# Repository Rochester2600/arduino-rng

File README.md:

Arduino random number generator using sha1 for hammering in randomness wether we need it or
want it.

The calibration routing is from the orignal code and helps deal with things that happen
to transistors as they aged. Find a micro-E for an actual explanation that makes sense.

NOTE:
If you change the transistor to something with a different reverse bias threshold, the entire
thing can either get better or fall apart completely

Original project README
=============================================================================================

Arduino True Random Number Generator
----

Instructions for constructing the circuit can be found here: http://robseward.com/misc/RNG2/

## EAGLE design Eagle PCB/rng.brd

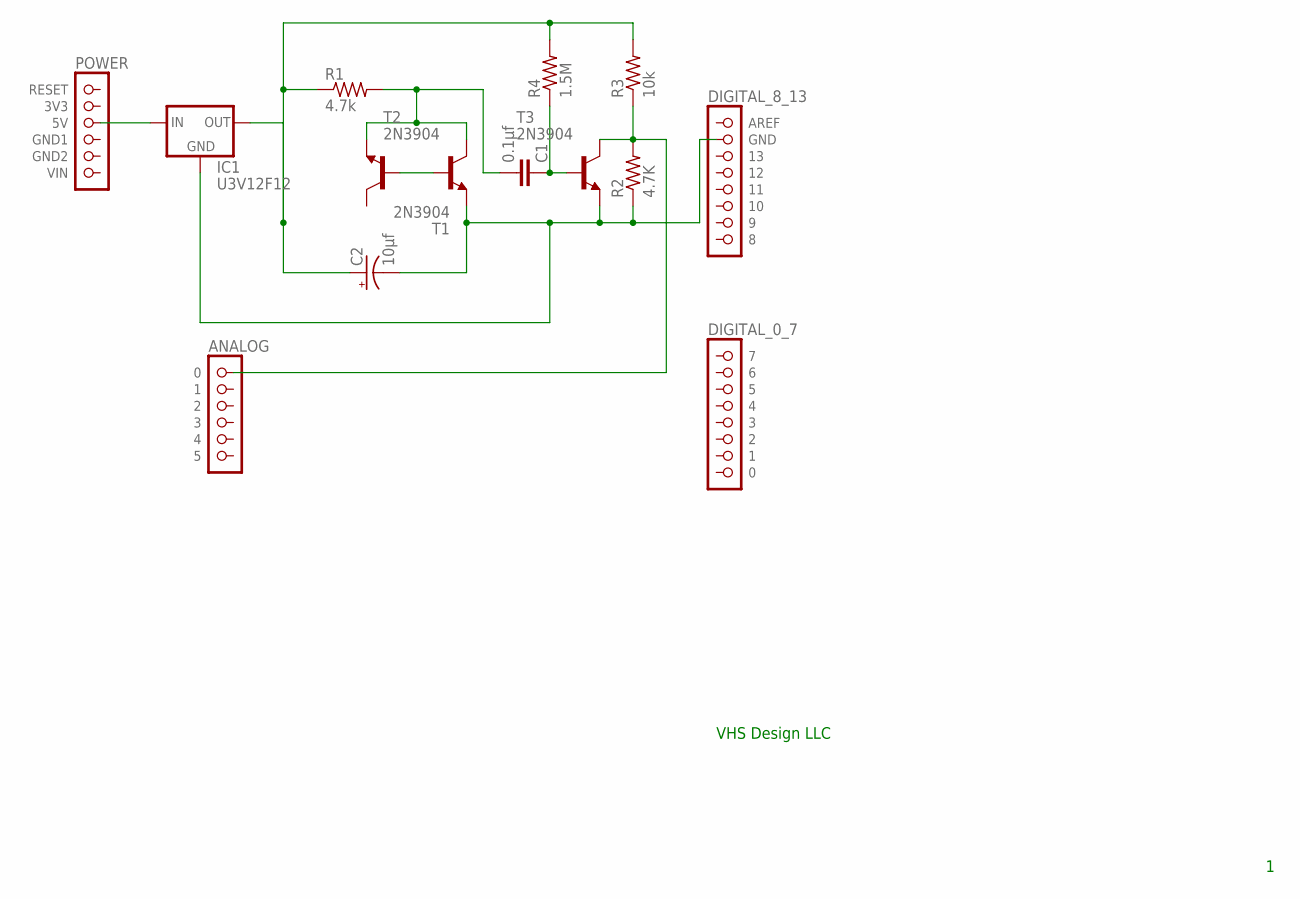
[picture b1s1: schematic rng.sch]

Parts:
C1: 0.1µf; C7.5B3
C2: 10µf; E2,5-6
IC1: U3V12F12; 78XXS
R1: 4.7k; 0204/7
R2: 4.7K; 0204/7
R3: 10k; 0204/7
R4: 1.5M; 0204/7
T1, T2, T3: 2N3904; TO92
U$1: POWER; 1X06
U$2: ANALOG; 1X06
U$3: DIGITAL_0_7; 1X08
U$4: DIGITAL_8_13; 1X08

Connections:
unnamed: T1.2 (B), T2.2 (B)
unnamed: C1.2, R1.2, T1.3 (E), T2.1 (C)
unnamed: C2.+, IC1.OUT, R1.1, R3.2, R4.2
unnamed: C1.1, R4.1, T3.2 (B)
unnamed: R2.2, R3.1, T3.1 (C), U$2.1 (0)
unnamed: IC1.IN, U$1.3 (5V)
unnamed: C2.-, IC1.GND, R2.1, T2.3 (E), T3.3 (E), U$4.2 (GND)

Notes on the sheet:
VHS Design LLC

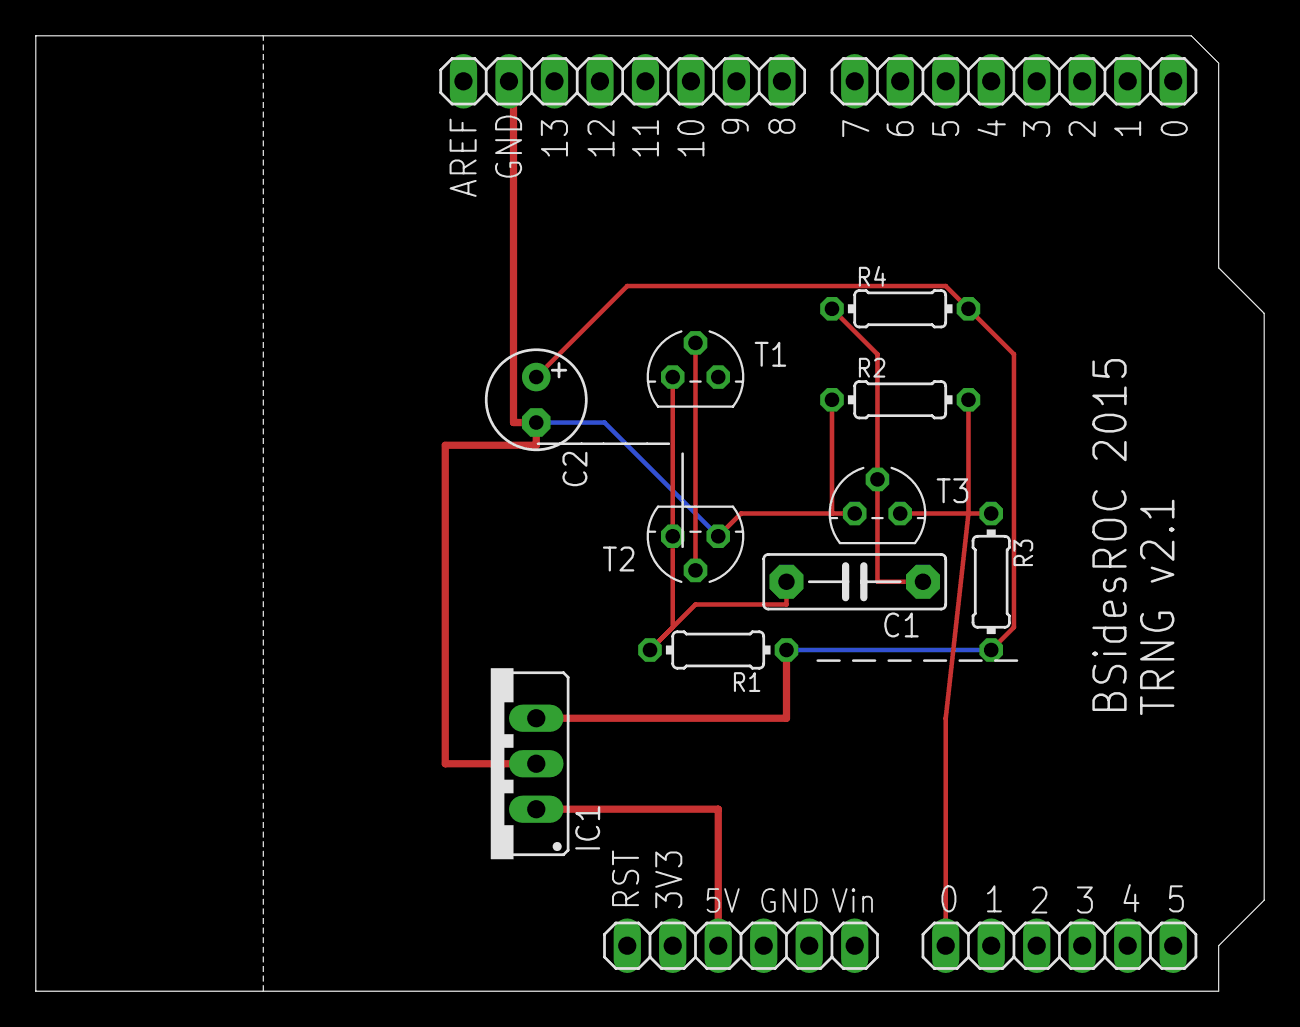
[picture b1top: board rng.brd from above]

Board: 2 copper layers, 68.6 x 53.3 mm, 14 parts (0 on the bottom side), 7 nets.

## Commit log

2015-04-25 tweak schematic and PCB for BSidesROC kits. can now run off 5V rather than 12V.
2015-04-25 add pee code
